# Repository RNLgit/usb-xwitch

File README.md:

# USB Hub

A programmable budget USB 1:2 multiplexer and HUB device (original name usb-xwitch). Features one 1:2 USB 3.1 switch and 4 Ch USB 2.0 remote 
controllable HUB. Controlling via on board micro USB or by Raspberry Pi UART. 

## CAD Setup (KiCad 6.0)

- Open ./sch/usb_xwitch.kicad_pro -> Schematics Editor 
- in Preferences -> Configure Path, add path name: "USB_XWITCH" and path: absolute address of the project (e.g. /Users/runnanl/src/usb-hub)

1. Channel Features

- Switch: USB 3.0 High Speed 1 Mux 2 switching. Additional physical control by push button switch.
- HUB: USB 2.0 HS 1:4 HUB. Individual remote control, power delivery and over current shutdown.
- HUB Expansion: UART daisy chain HUB capability.

2. Command via micro USB serial (default) or use by UART from Raspberry Pi (as a HAT)

## CAD Setup (KiCad 6.0)

- Open ./sch/usb_xwitch.kicad_pro -> Schematics Editor 
- in Preferences -> Configure Path, add path name: "USB_XWITCH" and path: absolute address of the project (e.g. /Users/runnanl/src/usb-hub)

## Hardware Overview

version: v0.2

PCBA front

PCBA rear

- CHS: USB3.0 1 mux 2. Port active indications. Switch button.
- CHH: USB2.0 HS 1x upstream USB-B to 4x downstream USB-A ports. Control via commands.
- Raspberry Pi compaticable header (10 Pins).
- Mountable as Raspberry Pi 2/3/4 HAT.

Power Supply:

12V 2A supplied by barrel jack (default unmounted) OR PWR screw terminal. Alternatively, 5V 3A DC power can directly
power 5V points from 10 Pin header. 

> **WARNING** : Only one power supply connected at the same time

## Software Overview

- pico software
- USB control protocols and commands
- UART control commands

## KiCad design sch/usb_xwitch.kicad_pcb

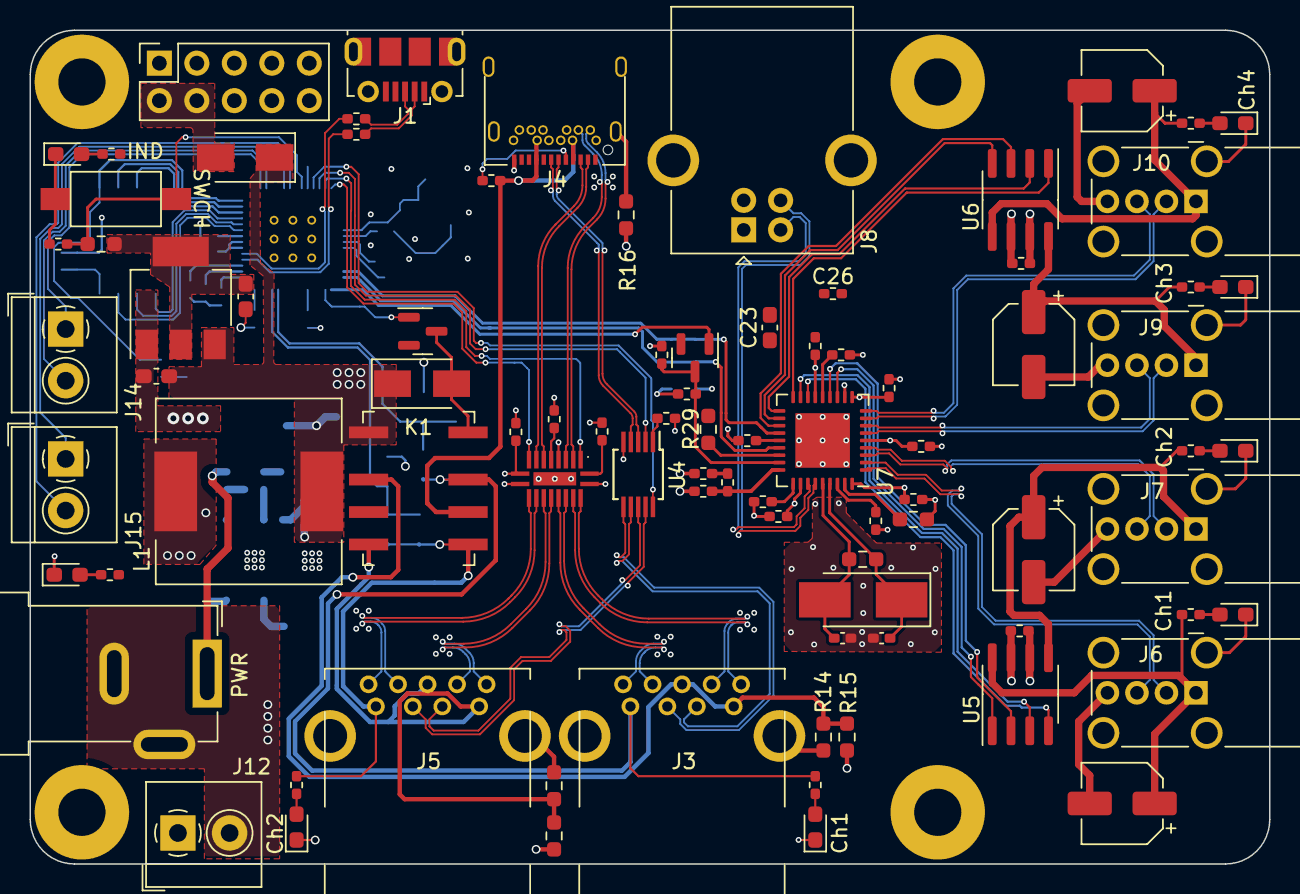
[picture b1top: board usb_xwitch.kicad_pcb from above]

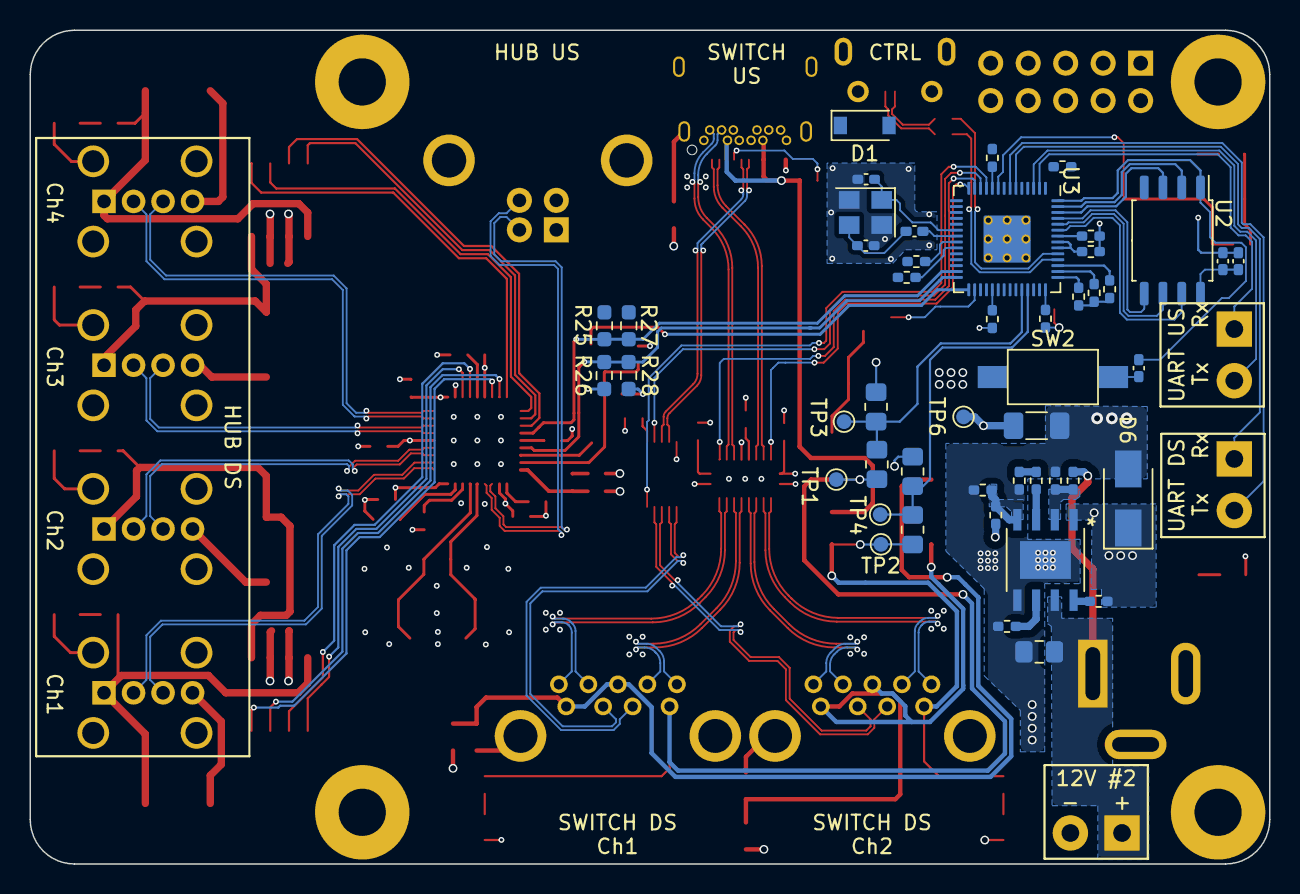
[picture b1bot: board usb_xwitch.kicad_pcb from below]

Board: 4 copper layers, 84.0 x 56.5 mm, 138 parts (47 on the bottom side), 112 nets.

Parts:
C1, C2, C3, C4, C5, C6, C7, C8, C9, C10, C11, C18, C19, C20, C21, C22, C24, C25, C27, C28, C29, C30, C37, C38, C41: 100n; R_0402_1005Metric_Pad0.72x0.64mm_HandSolder
C12, C13, C26, C32: 1u; R_0402_1005Metric_Pad0.72x0.64mm_HandSolder
C14: 2.2u; L_0402_1005Metric_Pad0.77x0.64mm_HandSolder
C15: 100n; L_0402_1005Metric_Pad0.77x0.64mm_HandSolder
C16, C17: 30pF; C_0402_1005Metric_Pad0.74x0.62mm_HandSolder
C23: 4.7u; C_0603_1608Metric_Pad1.08x0.95mm_HandSolder
C31, C33, C36, C40: 100u; CP_Elec_5x5.4
C34: DNP; R_0402_1005Metric_Pad0.72x0.64mm_HandSolder
C35, C39: 27p; C_0402_1005Metric_Pad0.74x0.62mm_HandSolder
C42: 22u; C_1206_3216Metric_Pad1.33x1.80mm_HandSolder
C43: 10u; C_0805_2012Metric_Pad1.18x1.45mm_HandSolder
C44: 150pF; R_0402_1005Metric_Pad0.72x0.64mm_HandSolder
C45, C46: 10u; C_0603_1608Metric_Pad1.08x0.95mm_HandSolder
D1: B5819W SL; D_SOD-123
D2, D4, D5, D8, D9, D10, D11, D12: 19-217/GHC-YR1S2/3T; D_0603_1608Metric_Pad1.05x0.95mm_HandSolder
D3, D6, D7: SS34; D_SMA
H1, H2, H3, H4: RPI Mounting Hole; MountingHole_3.2mm_M3_Pad
J1: USB_B_Micro; USB_Micro-B_Molex-105017-0001
J2: Barrel_Jack_Switch_Pin3Ring; BarrelJack_SCD556DCS113BM3G
J3, J5: USB3_A; USB3_A_AdamTech_USB-A3-S-RA
J4: USB_C_Receptacle; USB_TypeC_24Pin_ShouHan
J6, J7, J9, J10: USB_A; USB_A_Wuerth_614004134726_Horizontal
J8: USB_B; USB_B_OST_USB-B1HSxx_Horizontal
J12, J14, J15: Screw_Terminal_3.5mm; TerminalBlock_4Ucon_1x02_P3.50mm_Horizontal
J13: Conn_02x05_Odd_Even; PinSocket_2x05_P2.54mm_Vertical
K1: Relay_DPDT_Panasonic_AGQ200A4H
L1: 15u; L_12x12mm_H6mm
MUX1: PI3USB302-A; USB_MUX_DEMUX_PI3USB302-A
Q1, Q2: 2N7002P; SOT-23
R1, R2: 27.4R; R_0402_1005Metric_Pad0.72x0.64mm_HandSolder
R3, R4: 1K; L_0402_1005Metric_Pad0.77x0.64mm_HandSolder
R5: 470R; R_0402_1005Metric_Pad0.72x0.64mm_HandSolder
R6, R25, R26, R29: 10K; R_0603_1608Metric_Pad0.98x0.95mm_HandSolder
R7, R8, R36, R37, R38, R39: 330; R_0402_1005Metric_Pad0.72x0.64mm_HandSolder
R9: 56K; R_0402_1005Metric_Pad0.72x0.64mm_HandSolder
R10, R11: 18K; R_0805_2012Metric_Pad1.20x1.40mm_HandSolder
R12, R13: 33K; R_0805_2012Metric_Pad1.20x1.40mm_HandSolder
R14, R15, R16, R17, R18: 0R; R_0603_1608Metric_Pad0.98x0.95mm_HandSolder
R19, R20, R21, R24, R30, R33, R35: 100K; R_0402_1005Metric_Pad0.72x0.64mm_HandSolder
R22: 12K; R_0603_1608Metric_Pad0.98x0.95mm_HandSolder
R23: 1M; R_0603_1608Metric_Pad0.98x0.95mm_HandSolder
R27, R28: 100K; R_0603_1608Metric_Pad0.98x0.95mm_HandSolder
R31: 24.9k; R_0402_1005Metric_Pad0.72x0.64mm_HandSolder
R32: 210k; R_0402_1005Metric_Pad0.72x0.64mm_HandSolder
R34: 40.2K; R_0402_1005Metric_Pad0.72x0.64mm_HandSolder
R40: 510; R_0402_1005Metric_Pad0.72x0.64mm_HandSolder
SW1, SW2: C2689642; SW_SPST_CK_PTS636_SP43_SMTR
TP1, TP2, TP3, TP4, TP6: TestPoint; TestPoint_Pad_D1.0mm
U2: W25Q64JVSSIQ; SOIC-8_5.23x5.23mm_P1.27mm
U3: RP2040; RP2040-QFN-56
U4: FSUSB42MUX; MSOP-10_3x3mm_P0.5mm
U5, U6: MIC2026-1BM; SOIC-8_3.9x4.9mm_P1.27mm
U7: USB2514B_Bi; QFN-36-1EP_6x6mm_P0.5mm_EP3.7x3.7mm
U8: MP1584EN-LF-Z
U9: NCP1117LPST33T3G; SOT-223-3_TabPin2
Y1: 12MHz; Crystal_SMD_3225-4Pin_3.2x2.5mm
Y2: 24MHz; Crystal_SMD_5032-2Pin_5.0x3.2mm_HandSoldering

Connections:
+1V1: C1.1, C2.1, C13.1, U3.23 (DVDD), U3.45 (VREG_VOUT), U3.50 (DVDD)
+3V3: C3.1, C4.1, C5.1, C6.1, C7.1, C8.1, C9.1, C10.1, C11.1, C12.1, C14.1, C15.1, C19.1, C20.1, C23.1, C24.1, C25.1, C26.1, C27.1, C28.1, C29.1, C30.1, C46.1, MUX1.1 (VDD), MUX1.6 (VDD), MUX1.10 (VDD), R6.1, R21.2, R25.1, R26.1, U2.8 (VCC), U3.1 (IOVDD), U3.10 (IOVDD), U3.22 (IOVDD), U3.33 (IOVDD), U3.42 (IOVDD), U3.43 (ADC_AVDD), U3.44 (VREG_IN), U3.48 (USB_VDD), U3.49 (IOVDD), U4.1 (VCC), U7.5 (VDDA33), U7.10 (VDDA33), U7.15 (VDD33), U7.23 (VDD33), U7.29 (VDDA33), U7.36 (VDDA33), U9.2 (VO)
+5V: C21.1, C22.1, C42.1, C45.1, D1.1 (K), D3.1 (K), D7.1 (K), K1.1, L1.2, R32.1, R40.1, TP6.1, U5.7 (IN), U6.7 (IN), U9.3 (VI)
/UART_RX_DN: J15.1, U3.6 (GPIO4)
/UART_RX_UP: J13.8, J14.1, U3.2 (GPIO0)
/UART_TX_DN: J15.2, U3.7 (GPIO5)
/UART_TX_UP: J13.10, J14.2, U3.3 (GPIO1)
/power_and_io/PWR_IN: C43.1, J2.1, J12.1, R30.2, U8.7 (VIN)
/usb2_hub/H_CTL_N: C39.1, R23.1, U7.32 (XTALOUT), Y2.2
/usb2_hub/H_CTL_P: C35.1, R23.2, U7.33 (XTALIN/CLKIN), Y2.1
/usb2_hub/H_D1_N: J6.2 (D-), U7.1 (USBDM_DN1/PRT_DIS_M1)
/usb2_hub/H_D1_P: J6.3 (D+), U7.2 (USBDP_DN1/PRT_DIS_P1)
/usb2_hub/H_D2_N: J7.2 (D-), U7.3 (USBDM_DN2/PRT_DIS_M2)
/usb2_hub/H_D2_P: J7.3 (D+), U7.4 (USBDP_DN2/PRT_DIS_P2)
/usb2_hub/H_D3_N: J9.2 (D-), U7.6 (USBDM_DN3/PRT_DIS_M3)
/usb2_hub/H_D3_P: J9.3 (D+), U7.7 (USBDP_DN3/PRT_DIS_P3)
/usb2_hub/H_D4_N: J10.2 (D-), U7.8 (USBDM_DN4/PRT_DIS_M4)
/usb2_hub/H_D4_P: J10.3 (D+), U7.9 (USBDP_DN4/PRT_DIS_P4)
/usb2_hub/H_U_N: J8.3 (D+), U7.31 (USBDP_UP)
/usb2_hub/H_U_P: J8.2 (D-), U7.30 (USBDM_UP)
/usb2_hub/OCSn1: U5.2 (FLGA), U7.13 (OCS_N1)
/usb2_hub/OCSn2: U5.3 (FLGB), U7.17 (OCS_N2)
/usb2_hub/OCSn3: U6.2 (FLGA), U7.19 (OCS_N3)
/usb2_hub/OCSn4: U6.3 (FLGB), U7.21 (OCS_N4)
/usb2_hub/PRTPWR1: U5.1 (ENA), U7.12 (PRTPWR1/BC_EN1)
/usb2_hub/PRTPWR2: U5.4 (ENB), U7.16 (PRTPWR2/BC_EN2)
/usb2_hub/PRTPWR3: U6.1 (ENA), U7.18 (PRTPWR3/BC_EN3)
/usb2_hub/PRTPWR4: U6.4 (ENB), U7.20 (PRTPWR4/BC_EN4)
/usb2_hub/RESETn: C34.1, Q2.3 (D), R21.1, U7.26 (RESET_N)
/usb2_hub/RST_CTL: Q2.1 (G), U3.29 (GPIO18)
/usb2_hub/SCL: R26.2, R28.1, U3.28 (GPIO17), U7.24 (SCL/SMBCLK/CFG_SEL0)
/usb2_hub/SDA: R25.2, R27.1, U3.27 (GPIO16), U7.22 (SDA/SMBDATA/NON_REM1)
/usb2_hub/V_Ch1: C31.1, J6.1 (VBUS), R36.1, U5.8 (OUTA)
/usb2_hub/V_Ch2: C33.1, J7.1 (VBUS), R37.1, U5.5 (OUTB)
/usb2_hub/V_Ch3: C36.1, J9.1 (VBUS), R38.1, U6.8 (OUTA)
/usb2_hub/V_Ch4: C40.1, J10.1 (VBUS), R39.1, U6.5 (OUTB)
/usb3_switch/PD-SU2: U3.11 (GPIO8), U4.10 (~OE)
/usb3_switch/PD-SU3: MUX1.2 (PD), U3.13 (GPIO10)
/usb3_switch/REL-CTL: Q1.1 (G), U3.30 (GPIO19)
/usb3_switch/RL1: D3.2 (A), K1.8, Q1.3 (D)
/usb3_switch/SD_1D_N: J3.2 (D-), U4.6 (HSD1-)
/usb3_switch/SD_1D_P: J3.3 (D+), U4.7 (HSD1+)
/usb3_switch/SD_1RX_N: J3.5 (SSRX-), MUX1.18 (Tx1-)
/usb3_switch/SD_1RX_P: J3.6 (SSRX+), MUX1.19 (Tx1+)
/usb3_switch/SD_1TX_N: J3.8 (SSTX-), MUX1.16 (Rx1-)
/usb3_switch/SD_1TX_P: J3.9 (SSTX+), MUX1.17 (Rx1+)
/usb3_switch/SD_2D_N: J5.2 (D-), U4.8 (HSD2-)
/usb3_switch/SD_2D_P: J5.3 (D+), U4.9 (HSD2+)
/usb3_switch/SD_2RX_N: J5.5 (SSRX-), MUX1.14 (Tx2-)
/usb3_switch/SD_2RX_P: J5.6 (SSRX+), MUX1.15 (Tx2+)
/usb3_switch/SD_2TX_N: J5.8 (SSTX-), MUX1.12 (Rx2-)
/usb3_switch/SD_2TX_P: J5.9 (SSTX+), MUX1.13 (Rx2+)
/usb3_switch/SEL-SU2: U3.12 (GPIO9), U4.2 (SEL)
/usb3_switch/SEL-SU3: MUX1.9 (SEL), U3.14 (GPIO11)
/usb3_switch/SU_D_N: J4.A7 (D-), U4.4 (D-)
/usb3_switch/SU_D_P: J4.A6 (D+), U4.3 (D+)
/usb3_switch/SU_R1_N: J4.B10 (RX1-), MUX1.4 (Tx-)
/usb3_switch/SU_R1_P: J4.B11 (RX1+), MUX1.3 (Tx+)
/usb3_switch/SU_T1_N: J4.A3 (TX1-), MUX1.8 (Rx-)
/usb3_switch/SU_T1_P: J4.A2 (TX1+), MUX1.7 (Rx+)
/usb3_switch/SW-INTR: C18.1, R6.2, SW1.2 (B), U3.9 (GPIO7)
/usb3_switch/VBUS_1_1: J3.1 (VBUS), K1.7, R7.1, R10.1, TP1.1
/usb3_switch/VBUS_1_2: J5.1 (VBUS), K1.5, R8.1, R11.1, TP2.1
/usb3_switch/V_1_1: R10.2, R12.1, TP3.1, U3.38 (GPIO26_ADC0)
/usb3_switch/V_1_2: R11.2, R13.1, TP4.1, U3.39 (GPIO27_ADC1)
/xwitch_controller/GPIO25_LED: R5.1, U3.37 (GPIO25)
/xwitch_controller/QSPI_SCLK: U2.6 (CLK), U3.52 (QSPI_SCLK)
/xwitch_controller/QSPI_SD0: U2.5 (DI(IO0)), U3.53 (QSPI_SD0)
/xwitch_controller/QSPI_SD1: U2.2 (DO(IO1)), U3.55 (QSPI_SD1)
/xwitch_controller/QSPI_SD2: U2.3 (IO2), U3.54 (QSPI_SD2)
/xwitch_controller/QSPI_SD3: U2.7 (IO3), U3.51 (QSPI_SD3)
/xwitch_controller/QSPI_SS: R3.1, U2.1 (~CS), U3.56 (QSPI_SS)
/xwitch_controller/USB_D+: J1.3 (D+), R1.2
/xwitch_controller/USB_D-: J1.2 (D-), R2.2
/xwitch_controller/XIN: C16.1, U3.20 (XIN), Y1.1
/xwitch_controller/XOUT: R4.1, U3.21 (XOUT)
GND: C1.2, C2.2, C3.2, C4.2, C5.2, C6.2, C7.2, C8.2, C9.2, C10.2, C11.2, C12.2, C13.2, C14.2, C15.2, C16.2, C17.2, C18.2, C19.2, C20.2, C21.2, C22.2, C23.2, C24.2, C25.2, C26.2, C27.2, C28.2, C29.2, C30.2, C31.2, C32.2, C33.2, C34.2, C35.2, C36.2, C37.2, C38.2, C39.2, C40.2, C42.2, C43.2, C45.2, C46.2, D2.1 (K), D4.1 (K), D5.1 (K), D6.2 (A), D8.1 (K), D9.1 (K), D10.1 (K), D11.1 (K), D12.1 (K), J1.5 (GND), J1.6 (Shield), J2.2, J2.3, J4.A1 (GND), J4.A12 (GND), J4.B1 (GND), J4.B12 (GND), J6.4 (GND), J6.5 (Shield), J7.4 (GND), J7.5 (Shield), J8.4 (GND), J8.5 (Shield), J9.4 (GND), J9.5 (Shield), J10.4 (GND), J10.5 (Shield), J12.2, J13.6, J13.9, K1.3, MUX1.5 (GND), MUX1.11 (GND), MUX1.20 (GND), Q1.2 (S), Q2.2 (S), R12.2, R13.2, R15.2, R16.1, R18.2, R20.1, R22.1, R24.1, R27.2, R28.2, R29.2, R31.2, R33.1, R34.2, R35.1, SW1.1 (A), SW2.1 (A), U2.4 (GND), U3.19 (TESTEN), U3.57 (GND), U4.5 (GND), U5.6 (GND), U6.6 (GND), U7.11 (TEST), U7.37 (VSS), U8.5 (GND), U8.EPAD, U9.1 (GND), Y1.2, Y1.4
unnamed: C17.1, R4.2, Y1.3
unnamed: C32.1, J8.1 (VBUS), R19.1
unnamed: C37.1, U7.34 (PLLFILT)
unnamed: C38.1, U7.14 (CRFILT)
unnamed: C41.1, D6.1 (K), L1.1, U8.1 (SW)
unnamed: C41.2, U8.8 (BST)
unnamed: C44.1, U8.3 (COMP)
unnamed: C44.2, R35.2
unnamed: D1.2 (A), J1.1 (VBUS)
unnamed: D2.2 (A), R5.2
unnamed: D4.2 (A), R7.2
unnamed: D5.2 (A), R8.2
unnamed: D7.2 (A), J13.2, J13.4
unnamed: D8.2 (A), R36.2
unnamed: D9.2 (A), R37.2
unnamed: D10.2 (A), R38.2
unnamed: D11.2 (A), R39.2
unnamed: D12.2 (A), R40.2
unnamed: J3.4 (GND), J3.7 (DRAIN), K1.2, R14.2, R15.1
unnamed: J3.10 (SHIELD), R14.1
unnamed: J4.A4 (VBUS), J4.A9 (VBUS), J4.B4 (VBUS), J4.B9 (VBUS), K1.6, R9.1
unnamed: J4.A5 (CC1), R9.2
unnamed: J4.S1 (SHIELD), R16.2
unnamed: J5.4 (GND), J5.7 (DRAIN), K1.4, R17.2, R18.1
unnamed: J5.10 (SHIELD), R17.1
unnamed: R1.1, U3.47 (USB_DP)
unnamed: R2.1, U3.46 (USB_DM)
unnamed: R3.2, SW2.2 (B)
unnamed: R19.2, R20.2, U7.27 (VBUS_DET)
unnamed: R22.2, U7.35 (RBIAS)
unnamed: R24.2, U7.28 (SUSP_IND/LOCAL_PWR/NON_REM0)
unnamed: R29.1, U7.25 (HS_IND/CFG_SEL1)
unnamed: R30.1, R31.1, U8.2 (EN)
unnamed: R32.2, R34.1, U8.4 (FB)
unnamed: R33.2, U8.6 (FREQ)

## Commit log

2022-06-12 update schematics
2022-06-14 trail usb data tx
2022-06-18 updated schematics
2022-06-19 add tp; ERC check
2022-06-19 added symbol and footprint
2022-06-20 updated lib using those in this repo
2022-06-20 updated sch with correct lib
2022-06-21 updated led resistor value
2022-06-22 updated pcb and sch
2022-06-23 changing schematics with one less mux and one more power cycle channel
2022-06-25 updated rpi connector, pico footprint and board dimension
2022-06-26 updated 3d model and pcb, sch finalize
2022-06-27 updated 3d models
2022-06-27 added tqfn_zb_20 3d model and other 3d models
2022-06-27 updated pcb
2022-06-28 pcb update
2022-06-30 added Panasonic relay lib for replacement
2022-06-30 added panasonic new relay symbol
2022-07-01 updated pcb to 2 sides
2022-07-02 new ck push button footprint added
2022-07-02 all components within rpi hat dimension
2022-07-02 fixed q2 not placed properly
2022-07-02 pcb updated
2022-07-03 usb gnd changed; wired mux1 all parts
2022-07-03 pcb in progress
2022-07-03 sch/usb_xwitch.kicad_pcb
2022-07-03 pcb routed exc gnd
2022-07-03 pcb copper poured
2022-07-07 updated release and manufacture
2022-07-08 added manufacture bom with replacement parts
2022-07-09 added image and md file
2022-07-09 led, res, sw, j footprint changed for manufacture
2022-07-10 update on new packaging
2022-07-10 udpate pcb
2022-07-10 updated gerber, bom and pos files
2022-07-11 manufacture data update
2022-07-11 added code for pico controller
2022-07-13 intr added
2022-07-16 update code with relay control
2022-07-16 added commsrepl
2022-07-18 link irq to cha control
2022-07-21 update serialrepl
2022-07-24 serial repl updates
2022-07-31 added rp2040 lib symbols; updated to 2 sch pages
2022-07-31 updated serial repl
2022-08-08 added pico sheet 2
2022-08-11 added dc dc step down for rpi2040
2022-08-14 update pico schematics
2022-08-15 update according to pico minimal design
2022-08-16 update crystal symbol/foorprint
2022-08-20 changed rp2040 to official kicad symbol and footprint
2022-08-20 updated rp2040 sch
2022-08-20 update usb sheet
2022-08-21 usb udates
2022-08-27 added usb2 usb3 mux in sch
2022-08-28 updated usb mux wiring
2022-08-28 added shouhan typec in lib
2022-08-28 updated usbc schematics
2022-08-29 more usb-c channels update
2022-08-30 updated pico pinout
2022-08-31 replaced old pico board connection to embedded rp2040
2022-09-01 added sch boxes
2022-09-03 start adding hub ic components and wiring
2022-09-05 added mic2026 power ic
2022-09-08 usb2515b ic power and comms circuit
2022-09-08 updated usb2514 output bus wire
2022-09-10 complete hub and split up sheets
2022-09-11 added MP1584 symbol and footprint
2022-09-11 mp1584
2022-09-11 updated power circuit
2022-09-11 annotated components
2022-09-12 drc checks and renaming
2022-09-12 wks style added
2022-09-12 updated power on leds, hub 4 LEDs and misc
2022-09-12 updated md
2022-09-14 updated 3d models, broken footprints, pcb re-import
2022-09-15 fix sch unexpect to gnd; usb to right angle; pcb boarder increased to pi size
2022-09-16 updated sch RESET pin ctrl
2022-09-17 correct usb footprints
2022-09-17 pcb layout update and some res package changed
2022-09-18 update pcb
2022-09-18 pcb layout update
2022-09-18 update component layout
2022-09-19 update components layout
2022-09-20 rearrange layout to fit
2022-09-21 component layout all in board
2022-09-21 update label for easy routing differential pair
2022-09-23 wrong wiring fixed on usb switch; update layout
2022-09-24 barrel jack for dc power added
2022-09-24 switch downstream differential pairs
2022-09-25 new differential layout meth
2022-09-26 more detailed readme
2022-09-27 usb2 routing
2022-09-27 updated usb layout
2022-09-28 routing power area
2022-09-29 thermal pad added
2022-09-30 more polygon area fill
2022-10-01 layout usb hub
2022-10-02 rp2040 routing added
2022-10-02 more IC layout updates
2022-10-03 gnd layer and pwr layer added
2022-10-04 updated drc annular clearance
2022-10-05 plenty pf DRC fixing
2022-10-06 clear drc and warnings
2022-10-06 v02 gerber and manufacturing
2022-10-08 init rp2040 software for v0.2
2022-10-08 added uart comms initial
2022-10-09 added uart rx threading
2022-10-10 added more DNF components for easy debugging
2022-10-12 more further away vias; new release BoM, Gerber, CPL
2022-10-15 crc added
2022-10-16 updated cpl.csv for quote
2022-10-18 readme updated
2022-10-18 readme resolve conflict
2022-10-27 i2c usbhub update
2022-11-03 conf
2022-11-03 HUB address register and defaults added
2022-11-06 correct switch set check
2022-11-08 more i2c
2022-11-13 updated block read / write
2022-11-13 updates on init hub
2022-11-14 update on mfg str, block write
2022-11-15 usb hub on off functioning
2022-11-15 usb-xwitch sw 0.2 a1
2022-11-15 readme updated v0.2 a1
2022-11-20 added daisy chain msg format initial
2022-11-24 conf update
2022-11-27 daisy chain update
2022-12-01 chain hub code update
2022-12-06 update daisy chain msg
2022-12-15 daisy chain discovery update
2022-12-23 updated daisychain scan signal
2023-01-12 daisy chain broadcast function updated
2023-01-15 more daisy chain get command
2023-01-25 dc daisy chain discovery
2023-01-26 now total hubs reflect true value
2023-01-27 get hub chain function
2023-01-27 added get_hubs to query all hubs
2023-01-27 updated set hub chain
2023-01-29 set hub chain
2023-01-29 set hubs completion
